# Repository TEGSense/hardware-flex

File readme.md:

# TEG Sense Board

This is a thermoelectric generator (TEG) boost converter used to power a connected battery or capacitor to periodically operate a microcontroller reading from a biometric sensor to compute blood oxygen saturation. That was a big sentence!

This is the second iteration of the TEGSense board, with some schematic fixes and redesigned for a smaller flex board with bigger contacts for easy printing of conductive traces.
It is intended to be connected to a print-friendly version of the [SpO2 board](https://github.com/TEGSense/hardware-spo2-flex) and a [flex capacitor bank](https://github.com/TEGSense/hardware-flex-capboard).

## License

Shield: [![CC BY-SA 4.0][cc-by-sa-shield]][cc-by-sa]

This work is licensed under a
[Creative Commons Attribution-ShareAlike 4.0 International License][cc-by-sa].

[![CC BY-SA 4.0][cc-by-sa-image]][cc-by-sa]

[cc-by-sa]: http://creativecommons.org/licenses/by-sa/4.0/
[cc-by-sa-image]: https://licensebuttons.net/l/by-sa/4.0/88x31.png
[cc-by-sa-shield]: https://img.shields.io/badge/License-CC%20BY--SA%204.0-lightgrey.svg

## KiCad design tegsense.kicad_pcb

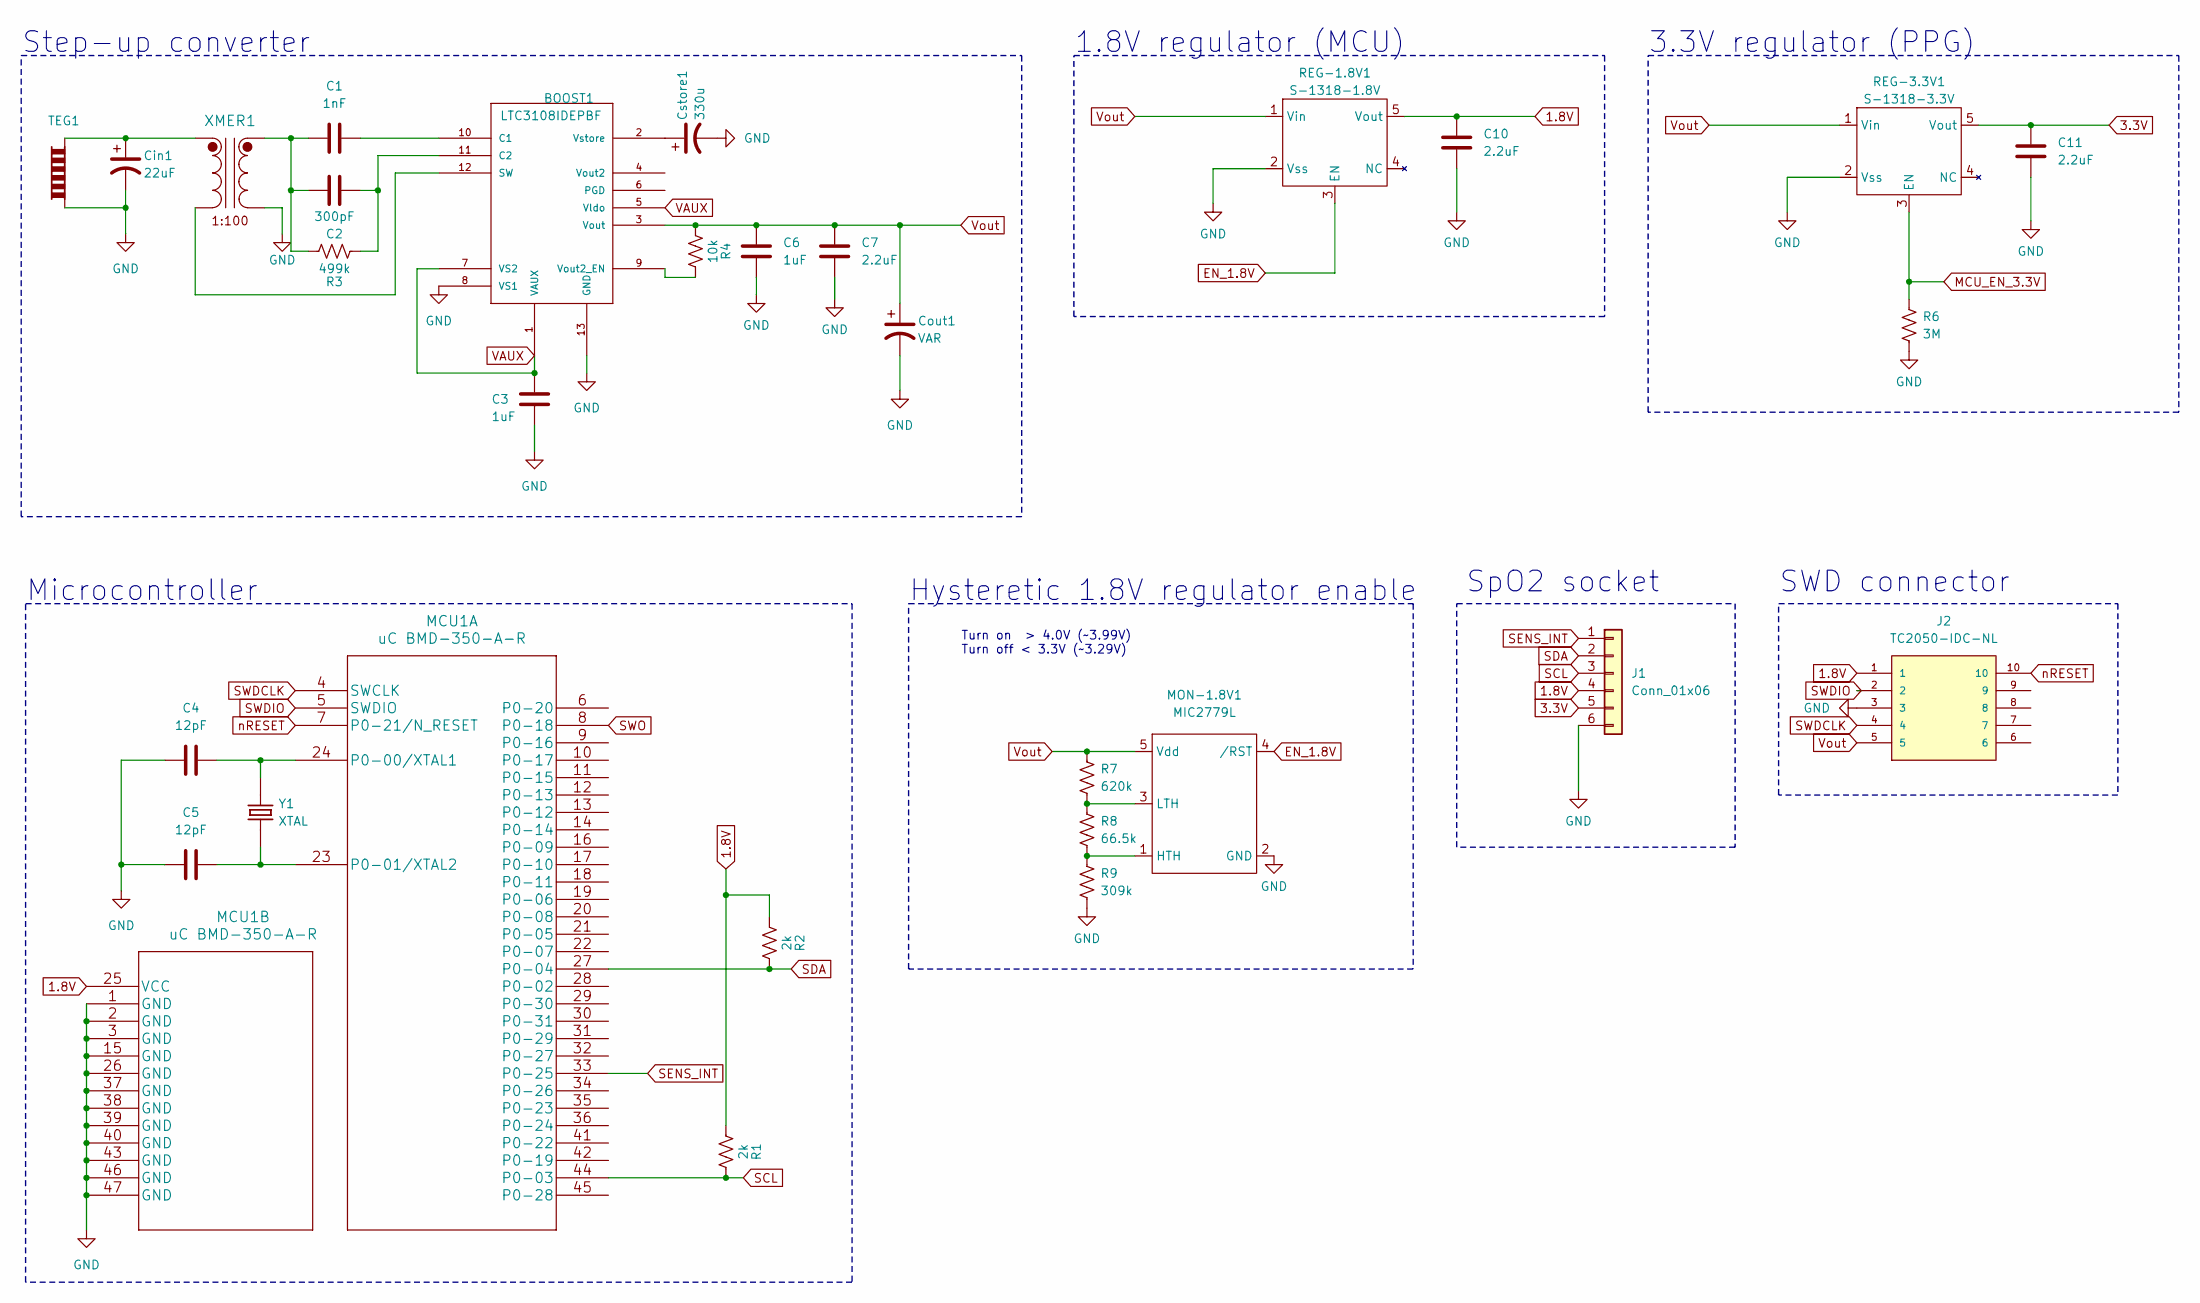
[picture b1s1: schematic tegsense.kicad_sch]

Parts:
BOOST1: LTC3108IDEPBF; DFN-12_DE
C1: 1nF; C_0402_1005Metric
C2: 300pF; C_0402_1005Metric
C3, C6: 1uF; C_0402_1005Metric
C4, C5: 12pF; C_0402_1005Metric
C7, C10, C11: 2.2uF; C_0402_1005Metric
Cin1: 22uF; C_0402_1005Metric
Cout1: VAR; PinSocket_1x02_P2.54mm_Vertical
Cstore1: 330u; CP_EIA-7343-31_Kemet-D
J1: Conn_01x06; PinSocket_1x06_P2.54mm_Vertical
J2: TC2050-IDC-NL
MCU1: uC BMD-350-A-R; BMD-350-A-R
MON-1.8V1: MIC2779L; SOT-23-5
R1, R2: 2k; R_0402_1005Metric
R3: 499k; R_0402_1005Metric
R4: 10k; R_0402_1005Metric
R6: 3M; R_0402_1005Metric
R7: 620k; R_0402_1005Metric
R8: 66.5k; R_0402_1005Metric
R9: 309k; R_0402_1005Metric
REG-1.8V1: S-1318-1.8V; SOT-23-5
REG-3.3V1: S-1318-3.3V; SOT-23-5
TEG1: TEG; PinSocket_1x02_P2.54mm_Vertical
XMER1: LPR6235-752SMLC
Y1: XTAL; XTAL_ECS-.327-9-16-TR

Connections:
1.8V: C10.1, J1.4, J2.1, MCU1.25 (VCC), R1.1, R2.1, REG-1.8V1.5 (Vout)
3.3V: C11.1, J1.5, REG-3.3V1.5 (Vout)
EN_1.8V: MON-1.8V1.4 (/RST), REG-1.8V1.3 (EN)
GND: BOOST1.8 (VS1), BOOST1.13 (GND), C3.2, C4.1, C5.1, C6.1, C7.2, C10.2, C11.2, Cin1.2, Cout1.2, Cstore1.2, J1.6, J2.3, MCU1.1 (GND), MCU1.2 (GND), MCU1.3 (GND), MCU1.15 (GND), MCU1.26 (GND), MCU1.37 (GND), MCU1.38 (GND), MCU1.39 (GND), MCU1.40 (GND), MCU1.43 (GND), MCU1.46 (GND), MCU1.47 (GND), MON-1.8V1.2 (GND), R6.2, R9.2, REG-1.8V1.2 (Vss), REG-3.3V1.2 (Vss), TEG1.1, XMER1.3
MCU_EN_3.3V: R6.1, REG-3.3V1.3 (EN)
unnamed: BOOST1.2 (Vstore), Cstore1.1
unnamed: BOOST1.9 (Vout2_EN), R4.2
unnamed: BOOST1.10 (C1), C1.2
unnamed: BOOST1.11 (C2), C2.2, R3.2
unnamed: BOOST1.12 (SW), XMER1.2
unnamed: C1.1, C2.1, R3.1, XMER1.4
unnamed: C4.2, MCU1.24 (P0-00/XTAL1), Y1.2
unnamed: C5.2, MCU1.23 (P0-01/XTAL2), Y1.1
unnamed: Cin1.1, TEG1.2, XMER1.1
unnamed: MON-1.8V1.1 (HTH), R8.2, R9.1
unnamed: MON-1.8V1.3 (LTH), R7.2, R8.1
SCL: J1.3, MCU1.44 (P0-03), R1.2
SDA: J1.2, MCU1.27 (P0-04), R2.2
SENS_INT: J1.1, MCU1.33 (P0-25)
SWDCLK: J2.4, MCU1.4 (SWCLK)
SWDIO: J2.2, MCU1.5 (SWDIO)
SWO: MCU1.8 (P0-18)
VAUX: BOOST1.1 (VAUX), BOOST1.5 (Vldo), BOOST1.7 (VS2), C3.1
Vout: BOOST1.3 (Vout), C6.2, C7.1, Cout1.1, J2.5, MON-1.8V1.5 (Vdd), R4.1, R7.1, REG-1.8V1.1 (Vin), REG-3.3V1.1 (Vin)
nRESET: J2.10, MCU1.7 (P0-21/N_RESET)

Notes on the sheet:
SWD connector
1.8V regulator (MCU)
Step-up converter
3.3V regulator (PPG)
Microcontroller
Turn on > 4.0V (~3.99V) Turn off < 3.3V (~3.29V)
Hysteretic 1.8V regulator enable
SpO2 socket

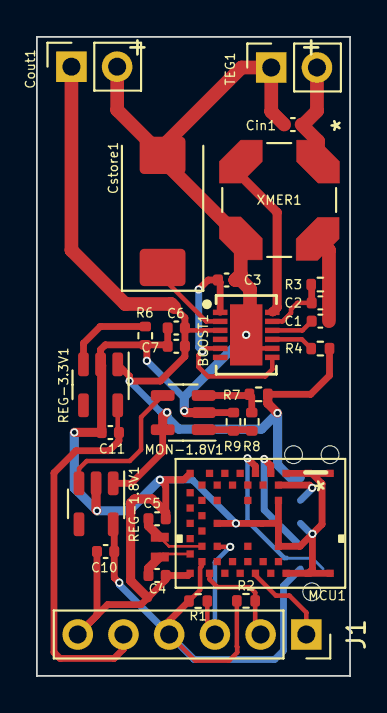
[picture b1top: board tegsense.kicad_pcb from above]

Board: 2 copper layers, 17.4 x 35.5 mm, 30 parts (1 on the bottom side), 24 nets.

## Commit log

2024-06-28 Initial.
2024-06-28 Clarified hardware version in readme.
2024-06-28 Updated KiCAD version and added image.
2024-06-28 Updated readme to link to relevant archives.
